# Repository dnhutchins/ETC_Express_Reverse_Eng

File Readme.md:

# ETC Express Control Surface Reverse Engineering

## Introduction

The ultimate goal of this work is to develop an interface to use the control surface from a legacy ETC Express 24/48 lighting controller as a modern EOSNomad compatible programming and fader wing. The CPU platform for the this board is not likely to be re-used for this project. This platform was developed in the late 1900s during the height of the Intel RISC based i960's popularity. This platform has been long abandoned, and although some tool-chains do exist, none seem to have been maintained beyond the early 2000s. As well no modern platform emulators seem to exist for the i960 architecture. Due to these challenges I decided to approach reverse engineering the interface port between the control surface and the CPU module, to hopefully implement either an OCS or HID based interface to a PC running EOS.

## Teardown & Analysis

### Internal Layout
Internal images are in the folder [internal-photos](internal-photos/)
### General System Layout
Overall, the console is comprised of two main components, the CPU/IO module, and the control surface. The two are connected by means of a 34 pin (2x17) connector. 
#### Control Surface
In the case of the 24/48 model I have access to, the surface consists of two main sections. These two sections are internally separate circuits, with each communicating with the CPU board independently. 
##### Fader & Bump Keys
On the left is the 48 fader & bump key module, consisting of 48 carbon film slide potentiometers as well as 48 momentary normally open "bump key" switches. Various multiplexers/decoders are used in conjunction with a PIC module to create a 2-wire communications link that is passed through directly to the CPU module (where it terminates at an Altera Flex FPGA) for decoding. With the bottom row of bump keys, there are 24 in-key LEDs, these are managed using an ICM7218BIPI LED control IC.
##### Design & Control keys, Master, and Cross faders
 On the right is the initial focus of this project. The primary control interface consisting of 70 N/O momentary key switches, 35 in-key LEDs, 5 carbon film slide potentiometers, and a touch-pad. These interface with the CPU module using 8 pins forming an 8 bit data bus,  7 pins as inputs to the 3 primary multiplexers/decoders, and 2 pins for control signals to the MAX150BCPP ADC. The ADC samples the state of the 5 fader potentiometers through a CD74HC4051-EP Analog Multiplexer and Demultiplexer. 
#### CPU Module
 This is the "brains" of the lighting console. This is an old embedded Intel design, employing fairly common chipsets for SuperIO, Floppy, Parallel, Ethernet, and VGA. Alongside the more common stuff, is an Altera Flex FPGA that likely handles the more specific stuff like DMX, ETCNet, MIDI, etc. 
##### Original firmware
This project aims to interface with the control surface, and discard the original CPU/IO module, so this is just listed as a reference in-case someone reads this and want's to port Doom to the express series console's CPU module or something.   
The last version of the firmware released: [Firmware](https://www.etcconnect.com/Support/Consoles/Legacy/Express/Software.aspx)

## Circuit Operation (control surface)
Since the two sections of the surface communicate to the CPU independently the will be treated as separate entities here. 
### Control Section
NOTE: This schematic is the product of tracing connections on this circuit, it is only meant to serve as a reference for signaling, it does not include descrete components such as bypass caps, pull up/down resistors, etc.

There is no external or internal clock signal in this section, states are read/written real-time, and individual ICs are clocked independently using (mostly) seperate signals.
#### Integrated Circuits
1. U1-U4 = 74HC4051 (Analog Multiplexer and Demultiplexers) [datasheet](datasheets/cd74hc4051-ep.pdf)
1. U5 = CD4066 (Quad Bilateral Switch) [datasheet](datasheets/cd4066b.pdf)
1. U6 = 74LS138 (3-LINE TO 8-LINE DECODERS/DEMULTIPLEXER) [datasheet](datasheets/sn74s138a.pdf)
1. U7-U8 = 74LS374 (OCTAL EDGE-TRIGGERED FLIP-FLOP) [datasheet](datasheets/sn54ls373-sp.pdf)
1. U9 = 74LS245 (Octal Bus Transceiver With 3-State Outputs) [datasheet](datasheets/sn74ls245.pdf)
1. U10 = 74LS08 (Quad 2-Input AND Gate) [datasheet](datasheets/74F08-196092.pdf)
1. U11-U12 = 74LS156 (DUAL 2-LINE TO 4-LINE DECODERS/DEMULTIPLEXER) [datasheet](datasheets/sn74ls156.pdf)
1. U13 = 74LS373 (OCTAL D-TYPE TRANSPARENT LATCH) [datasheet](datasheets/sn54ls373-sp.pdf)
1. U14 = ICM7218 (8 Digit LED Display Driver) [datasheet](datasheets/ICM7218-ICM7228.pdf)
1. U15 = MAX150 (CMOS High Speed 8 Bit A/D Converter with Reference and Track/Hold) [datasheet](datasheets/MAX150_MX7820-3468900.pdf)
1. U16 = LM358 (Dual Operational Amplifier) [datasheet](datasheets/lm358.pdf)
#### 8-bit Bus
1. Connection to the CPU module is buffered via U9.
1. Pin 19 from the interface connector selects the direction of U9 as well as RD/WR on U15
1. The bus sets U7 and U8, SN74LS374, to select which CD74HC4051-EP analog multiplexer/demultiplexer is enabled 
	* (One mux/demux is used to decode the analog faders, as well as additional mux/demuxes for additional faders not installed in the 24/48 I have access to)
1. U13 sets the bus, this appears to be used to decode key presses
1. The bus sets U14 used to drive the in-key leds
1. U15 sets the bus with value of the fader being routed via the analog mux/demux

#### Digital Muxes (Addressing and Keyboard scanning)
1. U6 - SN74LS138 (3-LINE TO 8-LINE DECODERS/DEMULTIPLEXER)
	* This demux is used to signal Write on U14, Cp on U7 and U8, CS on U15, and A2,B1 on either U11 or U12
	* Pins 11, 23, and 13 from the interface connector control the 3 address inputs
	* Pin 22 from the interface connector controls enable for U6 as well as U9
	* When either U11 or U12 is selected, U13 is activated via one of U10s AND gates, to latch key presses to the bus.
1. U11 - SN74LS156 (DUAL 2-LINE TO 4-LINE DECODERS/DEMULTIPLEXER)
	* Selects one of 8 keyboard "rows"
	* Pins 8, 26, and 28 from the interface connector control the 3 address inputs
	* Chip enable is from U6/0
1. U12 - SN74LS156 (DUAL 2-LINE TO 4-LINE DECODERS/DEMULTIPLEXER)
	* Selects one of 8 keyboard "rows" (4 of which route to the extrenal connector for a larger board configuration)
	* Pins 8, 26, and 28 from the interface connector control the 3 address inputs
	* Chip enable is from U6/1
#### Control Latches (Analog mux selection, addressing, and TP switching)
1. U7 - 74LS374 (OCTAL EDGE-TRIGGERED FLIP-FLOP) **Control register**
	* Operates SW1-4 of U5 CD4066 Quad Bilateral Switch
	* Address and selection signals to U4 Analog Multiplexer (Responsible for on-board faders and touch pad)
1. U8 - 74LS374 (OCTAL EDGE-TRIGGERED FLIP-FLOP) **Control register**
	* Address and selection signals to U4 Analog Multiplexer (Responsible for off-board faders, unused "external" connector
#### Keyboard "Column" Latches
1. U13 - 74LS373 (OCTAL D-TYPE TRANSPARENT LATCH)
	* U13 enables output to the bus, of the 8 columns for the row selected by U11/U12
	* This is enabled in the unlatched "following" state whenever either U11/U12 is selected by U6
	* LE is tied to VCC, so there is no actual latching, just switching the keyboard columns onto the bus.
#### Analog Muxes (Fader Section)
1. U1-U4 - 74HC4051 (Analog Multiplexer and Demultiplexers)
	* Faders are sampled using a single ADC, the analog muxes U1, U2, U3 and U4 are used to route one of up to 32 faders to the ADC.
	* U1, U2, and U3 all route to the external (unused on my board) connector.
	* U4 is connected to the Master, A, B, C, and D faders, as well as the touchpad.
	* U5 (quad analog switch) plays a role in routing the touch pad, where 2 of the switches short short the signal sides, including either pin 2 or 4 of U4 to ground, while the other switch on/off VCC (through a pull up resistor) to the other sides of the touch pad.
	* The output of the mux is connected to U15 through U16, to be sampled.
#### ADC
1. U15 - MAX150
	* Pin 16 from the interface connector controls the RD signal to the ADC
	* CS is driven from U6
	* Data is put directly on the bus
	* WR/WR follows the control from P19 along with the the buffer U9
#### LED Driver
1. U14 - ICM7218 (8 Digit LED Display Driver)
	* Pin 28 from the interface connector controls the MODE signal
	* U6/3 controls the WRITE signal
	* Mode is raised to send control word, then lowered to pulse in each of the 8 banks of 8 leds

## 34-pin "Face Panel Bus" Connector

This is the interface between the control surface and the CPU. The pins of this connector are connected internally as follows:

### Pinout

1. GND
2. U9 Pin-12 (B7)
3. U9 Pin-13 (B6)
4. GND
5. U9 Pin-16 (B3)
6. U9 Pin-17 (B2)
7. GND
8. U11 & U12 Pin-3 (B)
9. GND
10. N/C
11. U6 Pin-1 (A)
12. GND
13. U6 Pin-3 (C)
14. FADER-SUB-BOARD Data (PIC micro on fader board)
15. GND
16. U15 Pin-8 (_RD)
17. GND
18. VCC
19. U15 Pin-6 (_WR/RDY)
20. FADER-SUB-BOARD Data (PIC micro on fader board)
21. VCC
22. U6 Pin-4 (G1)
23. U6 Pin-2 (B)
24. VCC
25. N/C
26. U11 & U12 Pins-1,15 (1C,2C)
27. VCC
28. U11 & U12 Pin-13 (A)
29. U9 Pin-18 (B1)
30. VCC
31. U9 Pin-15 (B4)
32. U9 Pin-14 (B5)
33. VCC
34. U9 Pin-11 (B8)

## Misc. Links

https://github.com/ETCLabs/lighthack/?tab=readme-ov-file

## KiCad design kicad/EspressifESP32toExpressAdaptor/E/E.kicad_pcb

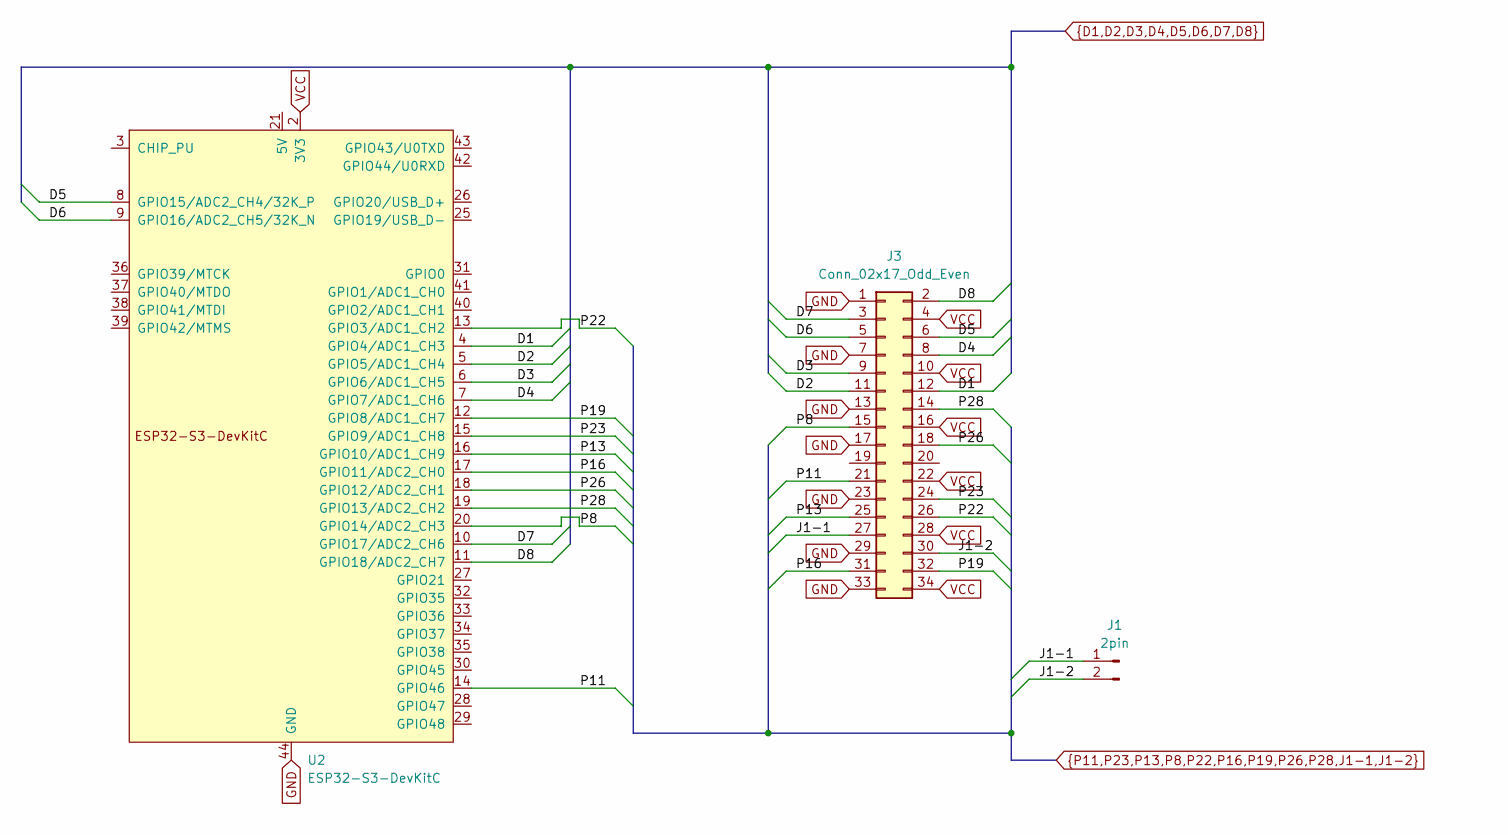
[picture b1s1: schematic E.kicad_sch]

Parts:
J1: 2pin; PinHeader_1x02_P2.54mm_Vertical
J3: Conn_02x17_Odd_Even; IDC-Header_2x17_P2.54mm_Vertical
U2: ESP32-S3-DevKitC

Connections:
D1: J3.12, U2.4 (GPIO4/ADC1_CH3)
D2: J3.11, U2.5 (GPIO5/ADC1_CH4)
D3: J3.9, U2.6 (GPIO6/ADC1_CH5)
D4: J3.8, U2.7 (GPIO7/ADC1_CH6)
D5: J3.6, U2.8 (GPIO15/ADC2_CH4/32K_P)
D6: J3.5, U2.9 (GPIO16/ADC2_CH5/32K_N)
D7: J3.3, U2.10 (GPIO17/ADC2_CH6)
D8: J3.2, U2.11 (GPIO18/ADC2_CH7)
GND: J3.1, J3.7, J3.13, J3.17, J3.23, J3.29, J3.33, U2.22 (GND), U2.23 (GND), U2.24 (GND), U2.44 (GND)
J1-1: J1.1, J3.27
J1-2: J1.2, J3.30
P8: J3.15, U2.20 (GPIO14/ADC2_CH3)
P11: J3.21, U2.14 (GPIO46)
P13: J3.25, U2.16 (GPIO10/ADC1_CH9)
P16: J3.31, U2.17 (GPIO11/ADC2_CH0)
P19: J3.32, U2.12 (GPIO8/ADC1_CH7)
P22: J3.26, U2.13 (GPIO3/ADC1_CH2)
P23: J3.24, U2.15 (GPIO9/ADC1_CH8)
P26: J3.18, U2.18 (GPIO12/ADC2_CH1)
P28: J3.14, U2.19 (GPIO13/ADC2_CH2)
VCC: J3.4, J3.10, J3.16, J3.22, J3.28, J3.34, U2.1 (3V3), U2.2 (3V3)

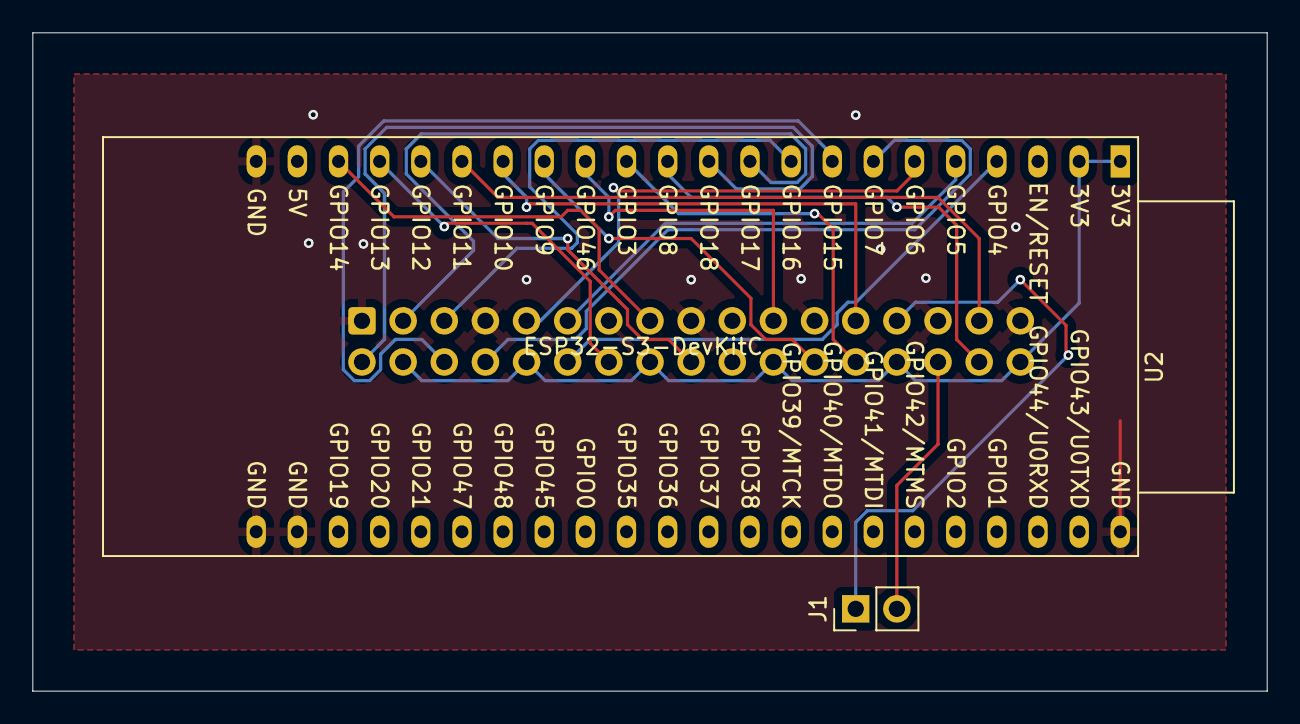
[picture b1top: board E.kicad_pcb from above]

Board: 2 copper layers, 76.2 x 40.6 mm, 3 parts (1 on the bottom side), 21 nets.

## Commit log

2025-01-13 Add R/E Schematic progress
2025-01-13 Add schematic file, and update svg
2025-01-13 Add full Kicad project, restructure, update Readme
2025-01-13 Update gitignore
2025-01-13 Update Schematic
2025-01-14 more schematic updates, another datasheet
2025-01-14 more datasheets
2025-01-14 More schematic work, more datasheets
2025-01-14 Fixed a wire
2025-01-14 converted some nets to busses for clarity
2025-01-14 More tidy-up work
2025-01-15 Schem update
2025-01-23 Working ESP32 micropython test code, schem updates, readme updates
2025-02-19 Add adapter PCB
